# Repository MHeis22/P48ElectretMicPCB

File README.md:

Ordered the PCBs from JLCPCB and components from Mouser. Initial test on 26.3.26 provided great results. Noticeably less bass heavy than the Fifine K688 which was used with XLR. Both microphones tested on a Scarlett 2i2 4th generation.

<!-- KICAD_DIFF_GEN_START -->
---
## 🛠 Technical Hardware Summary
*Autogenerated by GitHub Command Center*

### 📋 Project Overview
| Metric | Value |
| :--- | :--- |
| **Board Dimensions** | 37.0 x 51.01 mm |
| **Total Area** | 1887.24 mm² |
| **Layer Count** | 2 Copper Layers |
| **Total Components** | 27 |
| **SMD Components** | 21 |
| **THT Components** | 4 |
| **Unique Parts** | 25 |
| **KiCad Version** | 10.0.1 |

### 📐 Manufacturing & DRC
| Metric | Value |
| :--- | :--- |
| **Vias** | 235 Total (235 TH, 0 Blind, 0 Micro) |

### 📄 Architecture
- **Power Domains:** `GND`

### ⚙️ Mechanical
- **Mounting Holes:** 2 (H2 (MountingHole_2.7mm_M2.5_DIN965_Pad_TopBottom), H1 (MountingHole_2.5mm))

### 🚫 Do Not Populate (DNP)
- J3 (XLR3)

### 🧠 Core ICs & Modules
| Reference | Component | Function / Description |
| :--- | :--- | :--- |
| U1 | [OPA1678](https://octopart.com/search?q=OPA1678IDR&currency=EUR) | Low-Distortion Audio Operational Amplifiers, SOIC-8/VSSOP-8 |

### 🔌 Connectors & Interfaces
| Reference | Type | Component | Description |
| :--- | :--- | :--- | :--- |
| J2 | Connector | [MIC](https://octopart.com/search?q=TBC05-02-1-G-G&currency=EUR) | Generic connector, single row, 01x02, script generated |
| J1 | Connector | [XLR3](https://octopart.com/search?q=TBC05-03-1-G-G&currency=EUR) | Header for XLR pins |
| J3 | Connector | [XLR3](https://octopart.com/search?q=502-C3M&currency=EUR) | XLR Connector, Female, 3 Pins |

### 📏 Passive Components
| Component | Breakdown |
| :--- | :--- |
| Capacitor | 5x0603 and 5xOther |
| Diode | 3xOther |
| Resistor | 9x0603 |

---
<!-- KICAD_DIFF_GEN_END -->

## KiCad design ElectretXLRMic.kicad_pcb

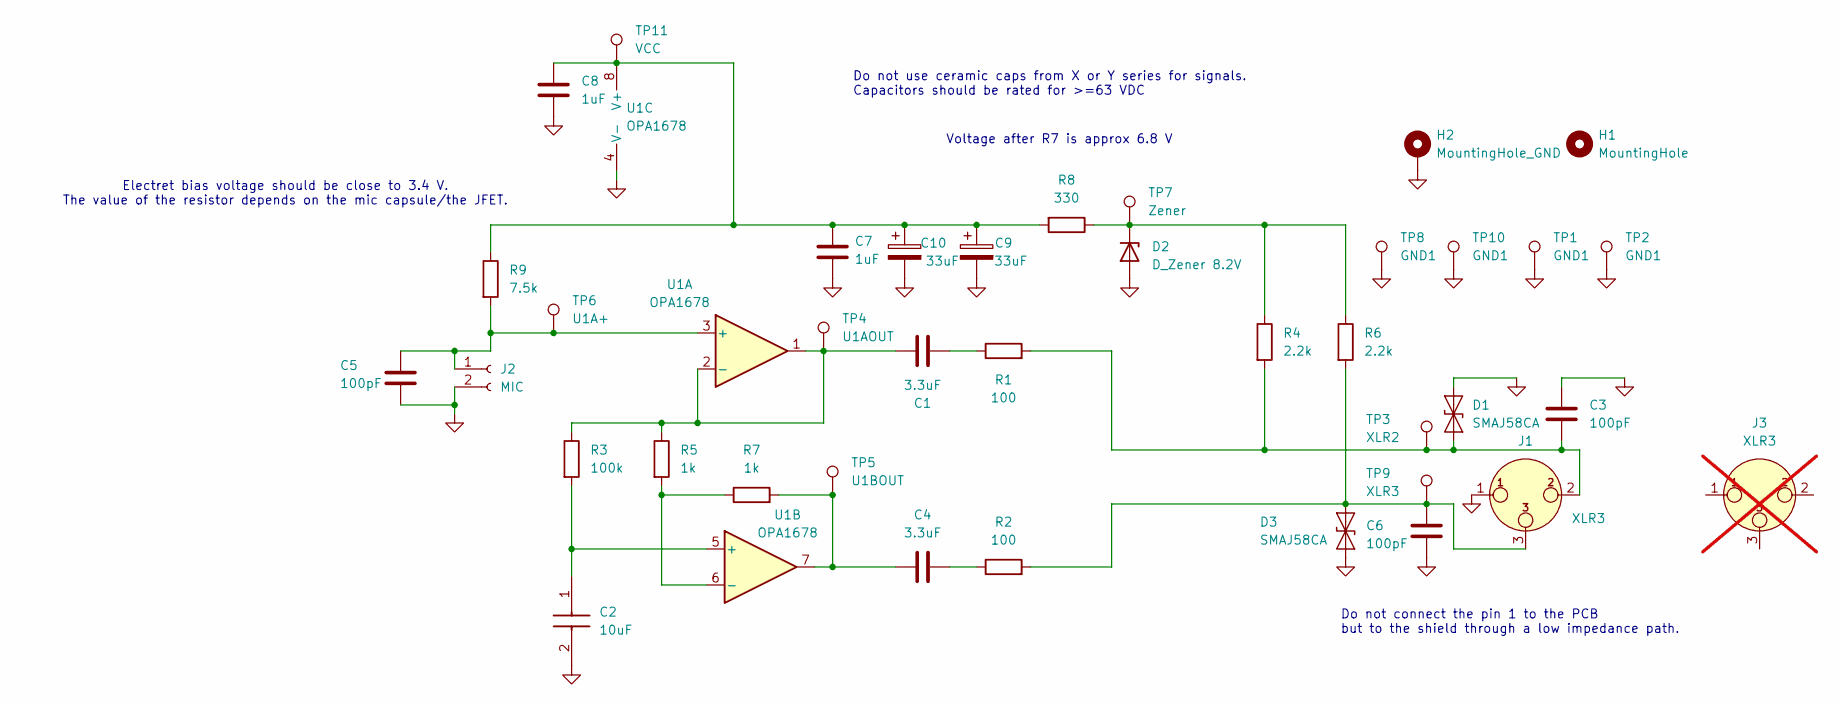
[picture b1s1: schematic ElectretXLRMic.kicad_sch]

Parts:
C1, C4: 3.3uF; C_Rect_L10.3mm_W5.7mm_P7.50mm_MKS4; Manufacturer_Part_Number R66DD4330AA6AJ
C2: 10uF; CAPAE660X850N; Manufacturer_Part_Number AEH0608100M050R
C3, C5, C6: 100pF; C_0603_1608Metric_Pad1.08x0.95mm_HandSolder; Manufacturer_Part_Number 0603N101F101CT
C7, C8: 1uF; C_0603_1608Metric_Pad1.08x0.95mm_HandSolder
C9, C10: 33uF; C_Elec_8x10.2; Manufacturer_Part_Number EEE-FK1J330V
D1, D3: SMAJ58CA; D_SMA; Manufacturer_Part_Number 710-824501581
D2: D_Zener 8.2V; D_SOD-123; Manufacturer_Part_Number BZT52-B8V2_R1_00001
H1: MountingHole; MountingHole_2.5mm
H2: MountingHole_GND; MountingHole_2.7mm_M2.5_DIN965_Pad_TopBottom
J1: XLR3; PinHeader_1x03_P2.54mm_Vertical; Manufacturer_Part_Number TBC05-03-1-G-G
J2: MIC; PinHeader_1x02_P2.00mm_Vertical; Manufacturer_Part_Number TBC05-02-1-G-G
J3: XLR3; Manufacturer_Part_Number 502-C3M; not fitted
R1, R2: 100; R_0603_1608Metric_Pad0.98x0.95mm_HandSolder; Manufacturer_Part_Number CRT0603ABY-1000ELF
R3: 100k; R_0603_1608Metric_Pad0.98x0.95mm_HandSolder; Manufacturer_Part_Number ERA-3AEB104V
R4, R6: 2.2k; R_0603_1608Metric_Pad0.98x0.95mm_HandSolder; Manufacturer_Part_Number ERA-3AEB222V
R5, R7: 1k; R_0603_1608Metric_Pad0.98x0.95mm_HandSolder; Manufacturer_Part_Number RP0603BRD071KL
R8: 330; R_0603_1608Metric_Pad0.98x0.95mm_HandSolder; Manufacturer_Part_Number ERA-3AEB331V
R9: 7.5k; R_0603_1608Metric_Pad0.98x0.95mm_HandSolder; Manufacturer_Part_Number ERA-1AEB752C
TP1, TP2, TP8, TP10: GND1; TestPoint_Pad_2.0x2.0mm
TP3: XLR2; TestPoint_Pad_2.0x2.0mm
TP4: U1AOUT; TestPoint_Pad_2.0x2.0mm
TP5: U1BOUT; TestPoint_Pad_2.0x2.0mm
TP6: U1A+; TestPoint_Pad_2.0x2.0mm
TP7: Zener; TestPoint_Pad_2.0x2.0mm
TP9: XLR3; TestPoint_Pad_2.0x2.0mm
TP11: VCC; TestPoint_Pad_2.0x2.0mm
U1: OPA1678; SOIC-8_3.9x4.9mm_P1.27mm; Manufacturer_Part_Number OPA1678IDR

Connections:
GND: C2.2 (-), C3.1, C5.2, C6.2, C7.2, C8.2, C9.2, C10.2, D1.2 (A2), D2.2 (A), D3.1 (A1), H2.1 (1_1), J1.1, J2.2, TP1.1 (1_1), TP2.1 (1_1), TP8.1 (1_1), TP10.1 (1_1), U1.4 (V-)
unnamed: C1.1, R1.1
unnamed: C2.1 (+), R3.2, U1.5 (+)
unnamed: C4.1, R7.2, TP5.1 (1_1), U1.7
unnamed: C4.2, R2.1
unnamed: C3.2, D1.1 (A1), J1.2, R1.2, R4.2, TP3.1 (1_1)
unnamed: D2.1 (K), R4.1, R6.1, R8.1, TP7.1 (1_1)
unnamed: C6.1, D3.2 (A2), J1.3, R2.2, R6.2, TP9.1 (1_1)
unnamed: C5.1, J2.1, R9.2, TP6.1 (1_1), U1.3 (+)
unnamed: C1.2, R3.1, R5.1, TP4.1 (1_1), U1.1, U1.2 (-)
unnamed: R5.2, R7.1, U1.6 (-)
unnamed: C7.1, C8.1, C9.1, C10.1, R8.2, R9.1, TP11.1 (1_1), U1.8 (V+)

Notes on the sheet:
Electret bias voltage should be close to 3.4 V. The value of the resistor depends on the mic capsule/the JFET.
Do not use ceramic caps from X or Y series for signals. Capacitors should be rated for >=63 VDC
Do not connect the pin 1 to the PCB but to the shield through a low impedance path.
Voltage after R7 is approx 6.8 V

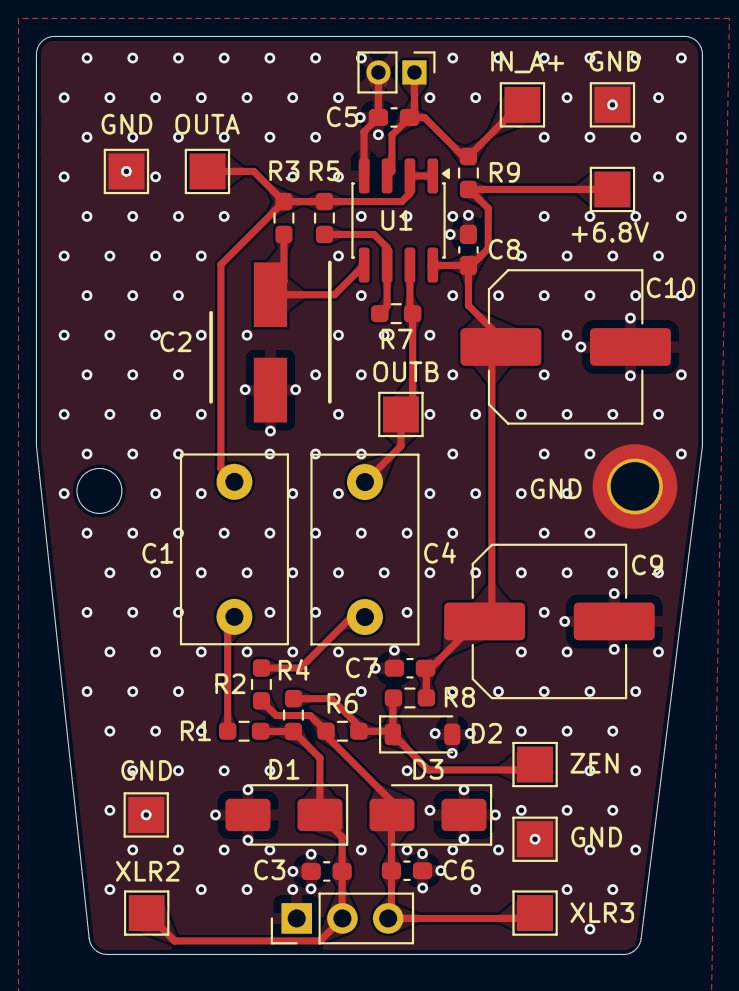
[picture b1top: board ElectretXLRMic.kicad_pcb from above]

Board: 2 copper layers, 37.0 x 51.0 mm, 38 parts (0 on the bottom side), 12 nets.

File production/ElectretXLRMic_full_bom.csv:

Qty,Reference,Value,Footprint,Manufacturer_Part_Number,Description
2,"C1, C4",3.3uF,Capacitor_THT:C_Rect_L10.3mm_W5.7mm_P7.50mm_MKS4,R66DD4330AA6AJ,Film Capacitors 63V 3.3 uF 105C 5% 2 Pin LS=7.5 mm AEC-Q200
1,C2,10uF,SamacSys_Parts:CAPAE660X850N,AEH0608100M050R,Aluminium Electrolytic Capacitors - SMD 50V 10uF 5000Hrs 20%
3,"C3, C5, C6",100pF,Capacitor_SMD:C_0603_1608Metric_Pad1.08x0.95mm_HandSolder,0603N101F101CT,Unpolarized capacitor
2,"C9, C10",33uF,Capacitor_SMD:C_Elec_8x10.2,EEE-FK1J330V,Polarized capacitor
2,"D1, D3",SMAJ58CA,Diode_SMD:D_SMA,710-824501581,"400W bidirectional Transient Voltage Suppressor, 58.0Vr, SMA(DO-214AC)"
1,D2,D_Zener 8.2V,Diode_SMD:D_SOD-123,BZT52-B8V2_R1_00001,Zener diode
1,J1,XLR3,Connector_PinHeader_2.54mm:PinHeader_1x03_P2.54mm_Vertical,TBC05-03-1-G-G,Header for XLR pins
1,J2,MIC,Connector_PinHeader_2.00mm:PinHeader_1x02_P2.00mm_Vertical,TBC05-02-1-G-G,"Generic connector, single row, 01x02, script generated"
1,J3,XLR3,,502-C3M,"XLR Connector, Female, 3 Pins"
2,"R1, R2",100,Resistor_SMD:R_0603_1608Metric_Pad0.98x0.95mm_HandSolder,CRT0603ABY-1000ELF,Resistor
1,R3,100k,Resistor_SMD:R_0603_1608Metric_Pad0.98x0.95mm_HandSolder,ERA-3AEB104V,Resistor
2,"R4, R6",2.2k,Resistor_SMD:R_0603_1608Metric_Pad0.98x0.95mm_HandSolder,ERA-3AEB222V,Resistor
2,"R5, R7",1k,Resistor_SMD:R_0603_1608Metric_Pad0.98x0.95mm_HandSolder,RP0603BRD071KL,Resistor
1,R8,330,Resistor_SMD:R_0603_1608Metric_Pad0.98x0.95mm_HandSolder,ERA-3AEB331V,Resistor
1,R9,7.5k,Resistor_SMD:R_0603_1608Metric_Pad0.98x0.95mm_HandSolder,ERA-1AEB752C,Resistor
1,U1,OPA1678,Package_SO:SOIC-8_3.9x4.9mm_P1.27mm,OPA1678IDR,"Low-Distortion Audio Operational Amplifiers, SOIC-8/VSSOP-8"

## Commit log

2026-03-13 Add initial note about assembly status
2026-03-15 Slight layout improvements
    [KiCad Version: 9.0.7]
2026-03-16 updated readme
    [KiCad Version: 9.0.7]
2026-03-16 Readme update
    [KiCad Version: 9.0.7]
2026-03-16 Readme update/test Slight changes to the schematic
    [KiCad Version: 9.0.7]
2026-03-16 Testing BOM-generator functionality
    [KiCad Version: 9.0.7]
2026-03-16 bom tool update/test
    [KiCad Version: 9.0.7]
2026-03-16 bom check
    [KiCad Version: 9.0.7]
2026-03-16 The TVS diodes had slightly different footprints, fixed now.
    [KiCad Version: 9.0.7]
2026-03-16 Test of gerber generator
    [KiCad Version: 9.0.7]
2026-03-16 Deleting unnecessary files
2026-03-16 Re commit of production files
    [KiCad Version: 9.0.7]
2026-03-17 Cleaned up repo, small changes to PCB layout
    [KiCad Version: 9.0.7]
2026-03-17 Removed .lck file
2026-03-17 Updated silkscreen thickness to be in accordance to JLC capabilities (0.153 mm thickness)
    [KiCad Version: 9.0.7]
2026-03-17 Small changes to the layout
    [KiCad Version: 9.0.7]
2026-03-25 Test of the circuit is done and final adjustments done for values. BOM has reduced amount of resistors and capacitors. Added 2.54 mm pitch wire terminals to BOM because getting the wires to the conne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
    [KiCad Version: 9.0.7]
2026-03-25 Revise README with testing and sourcing information
    Updated the README with details on PCB and component sourcing, initial testing results, and microphone comparison.
2026-03-25 Added new ibom, removed old.
    [KiCad Version: 9.0.7]
2026-03-25 readme
    [KiCad Version: 9.0.7]
2026-04-16 Added teardrops, made board slightly smaller and moved screw holes downwards.
    [KiCad Version: 10.0.1]
2026-04-16 Updated zone fill clearance
    [KiCad Version: 10.0.1]
2026-04-21 Cleaned up DRC, some routing optimizations, geographical annotation
    [KiCad Version: 10.0.1]
